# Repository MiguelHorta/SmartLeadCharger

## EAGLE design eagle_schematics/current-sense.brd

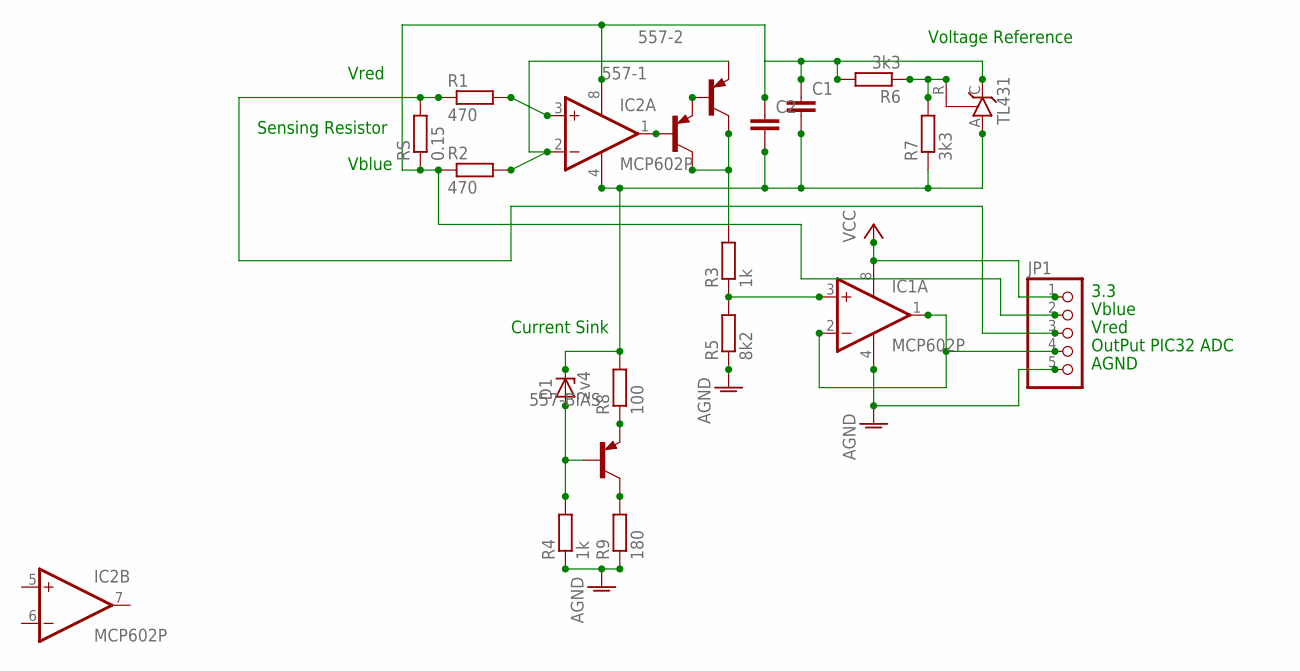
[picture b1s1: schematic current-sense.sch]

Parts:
557-1, 557-2, 557-BIAS: BC557A-PNP-TO92-EBC; TO92-EBC
C1, C2: C-EU075-032X103; C075-032X103
D1: 2v4; ZDIO-7.5
IC1, IC2: MCP602P; DIL08
JP1: PINHD-1X5; 1X05
R1, R2: 470; 0204/7
R3, R4: 1k; 0204/7
R5: 8k2; 0204/7
R6, R7: 3k3; 0204/7
R8: 100; 0204/7
R9: 180; 0204/7
RS: 0.15; VTA55
TL431: TL431CLP; TO92-CLP

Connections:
AGND: IC1.4 (V-), JP1.5, R5.1
unnamed: C1.2, C2.2, D1.C, IC2.4 (V-), R7.1, R8.2, TL431.A
unnamed: IC2.3 (+IN), R1.2
unnamed: 557-1.B, IC2.1 (OUT)
unnamed: 557-2.E, IC2.2 (-IN), R2.2
unnamed: 557-1.E, 557-2.B
unnamed: IC1.3 (+IN), R3.1, R5.2
unnamed: 557-1.C, 557-2.C, R3.2
unnamed: 557-BIAS.E, R8.1
unnamed: R6.1, R7.2, TL431.R
unnamed: 557-BIAS.C, R9.2
unnamed: 557-BIAS.B, D1.A, R4.2
unnamed: R4.1, R9.1
OUT: IC1.1 (OUT), IC1.2 (-IN), JP1.4
SN: C1.1, C2.1, IC2.8 (V+), JP1.2, R2.1, R6.2, RS.1, TL431.C
SP: JP1.3, R1.1, RS.2
VCC: IC1.8 (V+), JP1.1

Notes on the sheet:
3.3
AGND
OutPut PIC32 ADC
Vblue
Vred
Current Sink
Voltage Reference
Sensing Resistor

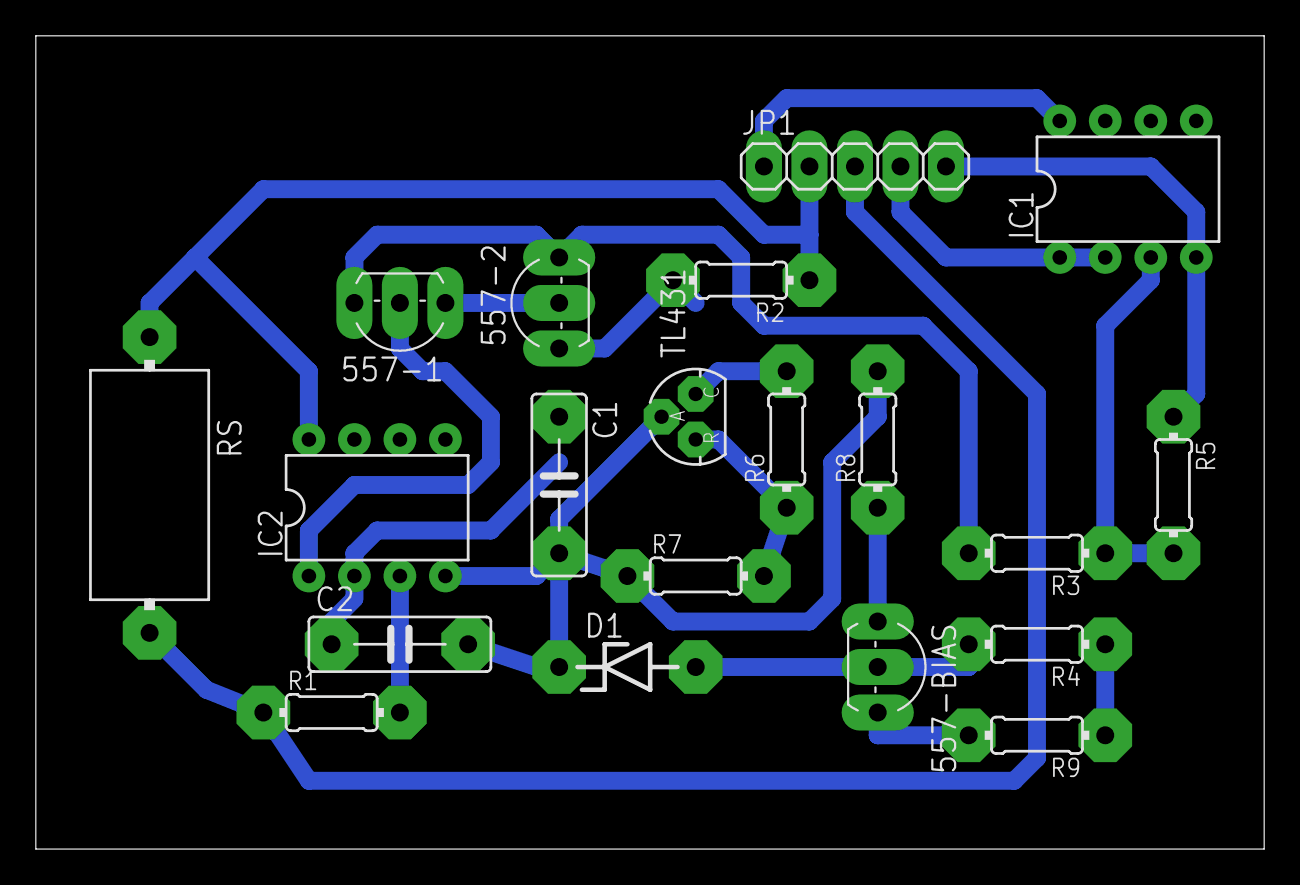
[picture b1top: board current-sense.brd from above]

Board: 2 copper layers, 68.6 x 45.4 mm, 20 parts (0 on the bottom side), 17 nets.

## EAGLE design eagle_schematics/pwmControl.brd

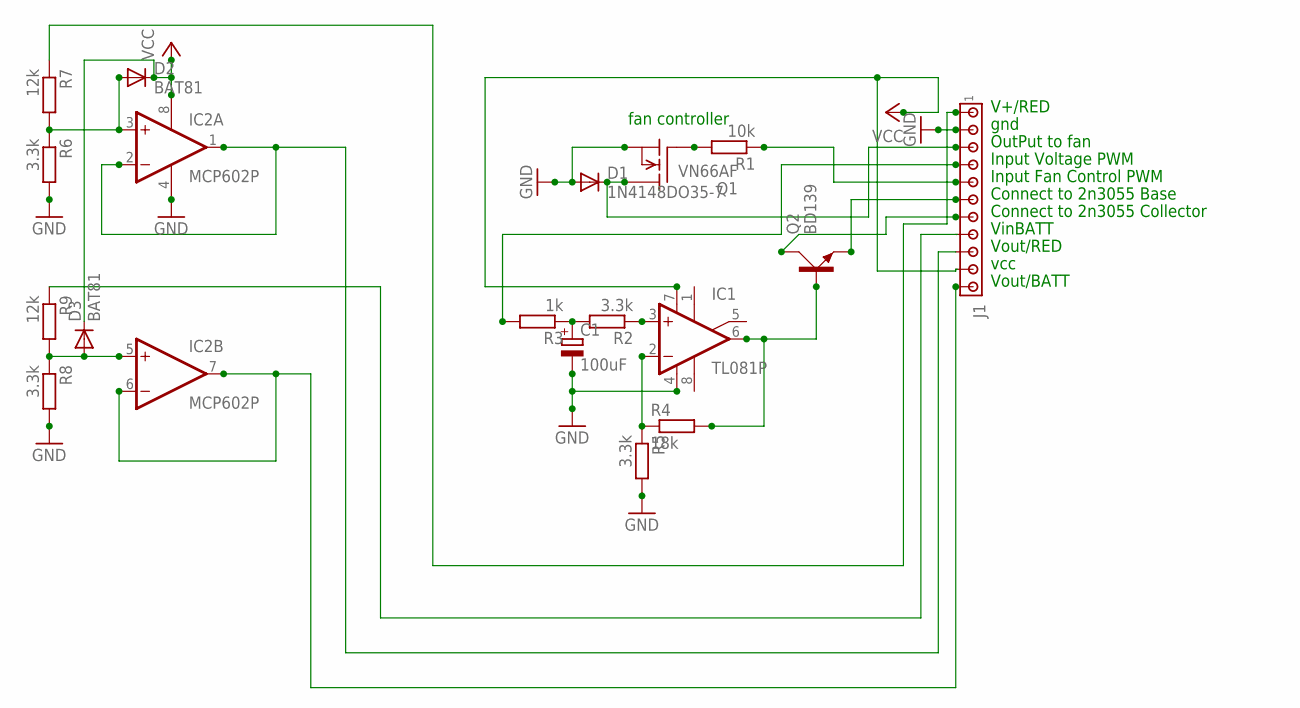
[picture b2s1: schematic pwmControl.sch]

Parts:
C1: 100uF; EB20D
D1: 1N4148DO35-7; DO35-7
D2, D3: BAT81; DO34-7
IC1: TL081P; DIL08
IC2: MCP602P; DIL08
J1: MTA11-156; 1X11MTA
Q1: VN66AF; TO202
Q2: BD139; TO126AV
R1: 10k; 0207/10
R2, R5, R6, R8: 3.3k; 0207/10
R3: 1k; 0207/10
R4: 18k; 0207/10
R7, R9: 12k; 0207/10

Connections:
2N3055BASE: J1.6, Q2.E
2N3055COL: J1.7, Q2.C
GND: C1.-, D1.A, IC1.4 (V-), IC2.4 (V-), J1.2, Q1.1 (S), R5.2, R6.2, R8.2
unnamed: Q1.2 (G), R1.2
unnamed: IC1.3 (+IN), R2.1
unnamed: C1.+, R2.2, R3.1
unnamed: IC1.2 (-IN), R4.1, R5.1
unnamed: IC1.6 (OUT), Q2.B, R4.2
unnamed: D2.A, IC2.3 (+IN), R6.1, R7.2
unnamed: D3.A, IC2.5 (+IN), R8.1, R9.2
OUTFAN: J1.5, R1.1
PWMFAN: D1.C, J1.3, Q1.3 (D)
PWMVOLTAGE: J1.4, R3.2
VCC: D2.C, D3.C, IC1.7 (V+), IC2.8 (V+), J1.10
VINBAT: J1.1, R7.1
VINRED: J1.8, R9.1
VOUTBATT: IC2.1 (OUT), IC2.2 (-IN), J1.9
VOUTRED: IC2.6 (-IN), IC2.7 (OUT), J1.11

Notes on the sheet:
fan controller
vcc
gnd
Input Fan Control PWM
OutPut to fan
Input Voltage PWM
Connect to 2n3055 Base
Connect to 2n3055 Collector
VinBATT
V+/RED
Vout/BATT
Vout/RED

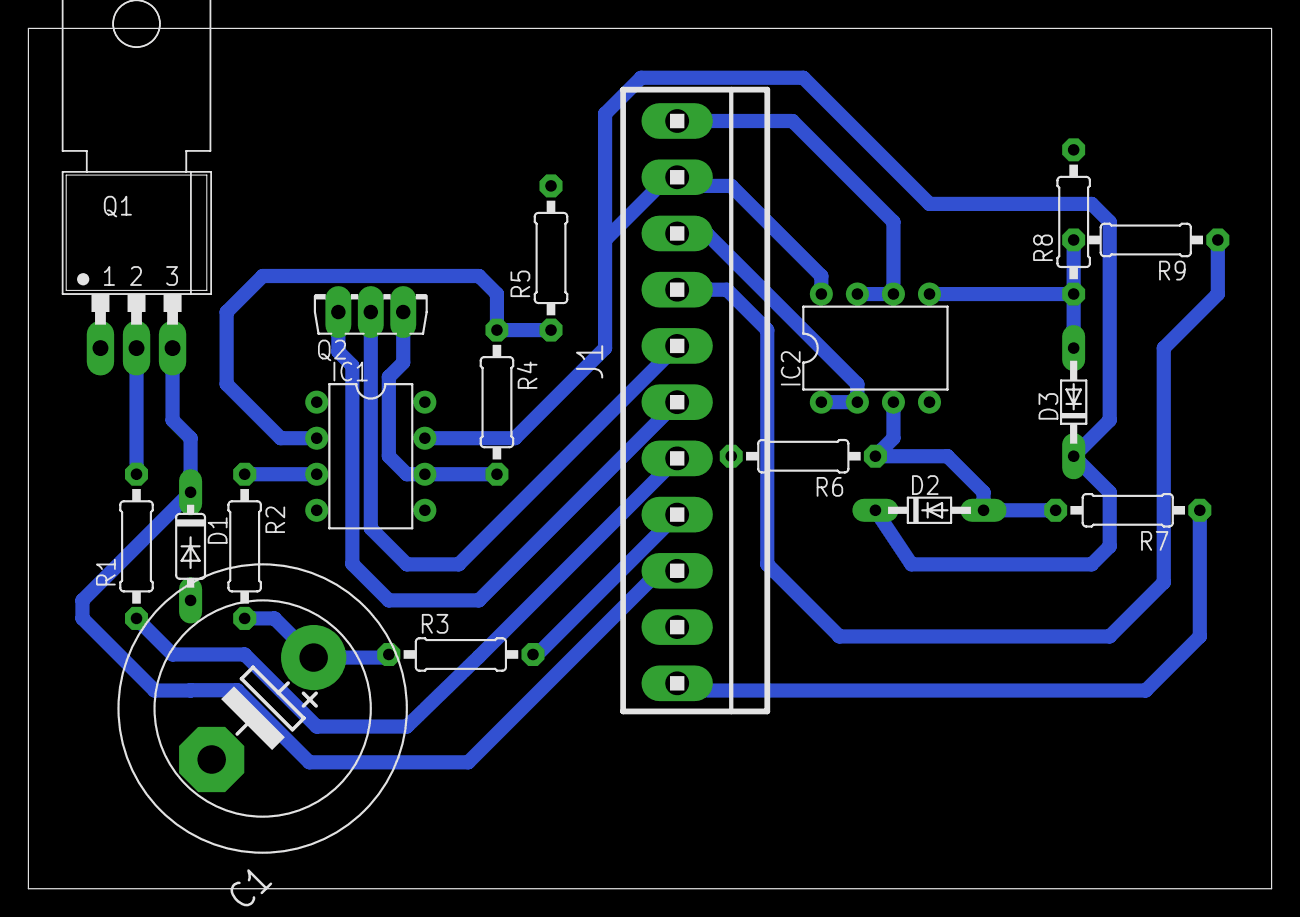
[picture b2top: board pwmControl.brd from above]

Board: 2 copper layers, 87.6 x 60.6 mm, 18 parts (0 on the bottom side), 18 nets.

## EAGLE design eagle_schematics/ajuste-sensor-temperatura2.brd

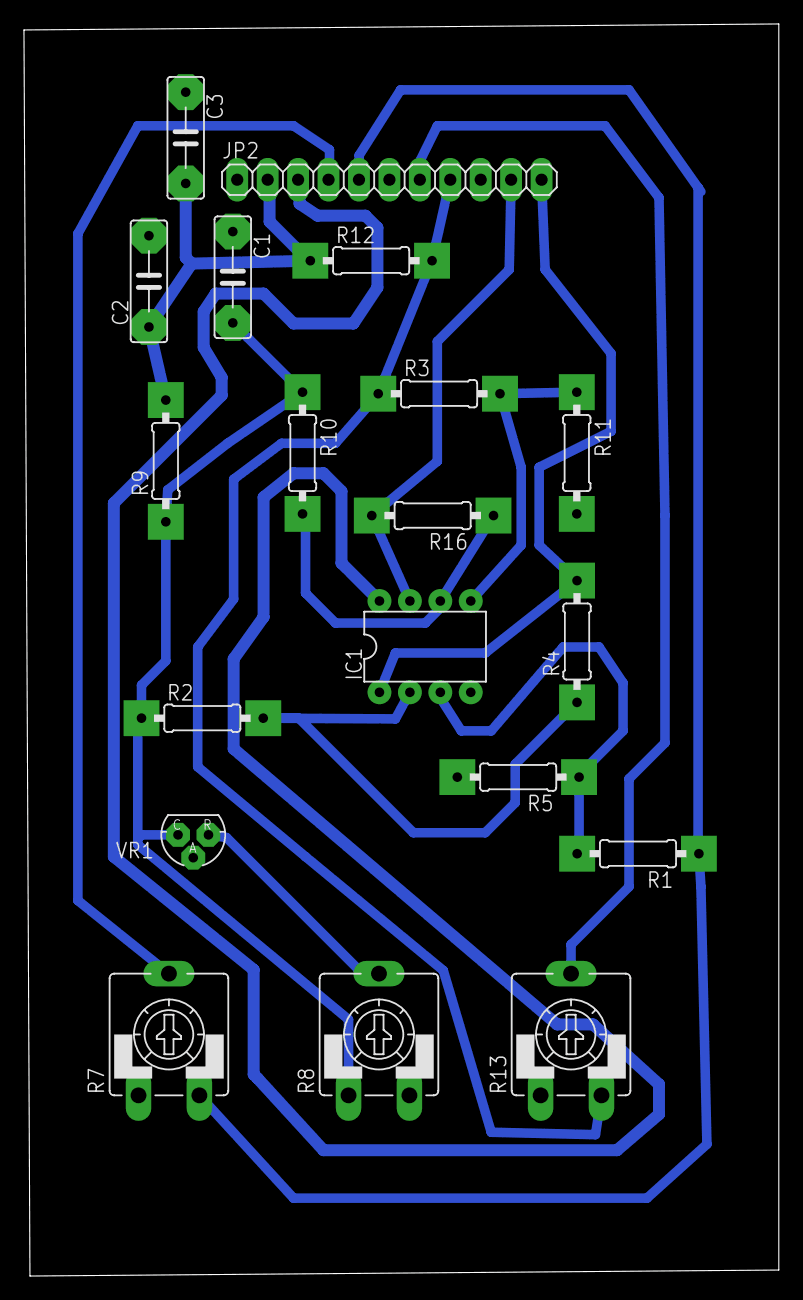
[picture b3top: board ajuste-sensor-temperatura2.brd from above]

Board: 2 copper layers, 63.0 x 104.5 mm, 19 parts (0 on the bottom side), 15 nets.

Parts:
C1, C2, C3: 0.01n; C7.5B3
IC1: MCP602P; DIL08
JP2: 1X11
R1, R2, R3, R10: 33k; 0207/10
R4, R5, R11, R16: 100k; 0207/10
R7, R13: 10k; CA9V
R8: 100; CA9V
R9: 120; 0207/10
R12: 330; 0207/10
VR1: 2.5V; TO92-CLP

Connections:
AGND: C1.1, C2.2, C3.1, IC1.4, JP2.1, JP2.6, JP2.9, R5.2, R7.A, R8.E, R11.2, R13.A, VR1.A
unnamed: IC1.3, R1.2, R5.1
unnamed: IC1.2, R2.2, R4.1
unnamed: JP2.5, R1.1, R7.E
unnamed: JP2.4, R7.S
unnamed: R8.S, VR1.R
unnamed: IC1.5, R3.2, R11.1
unnamed: IC1.6, R10.2, R16.1
unnamed: JP2.8, R3.1, R12.2, R13.E
unnamed: JP2.7, R13.S
unnamed: C1.2, R2.1, R8.A, R9.1, R10.1, VR1.C
OUT$1: IC1.1, JP2.11, R4.2
OUT$2: IC1.7, JP2.10, R16.2
S$1: C2.1, C3.2, JP2.2, R9.2, R12.1
VCC: IC1.8, JP2.3

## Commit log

2017-03-15 Commit de teste
2017-03-16 Finished ADC abstraction.
2017-03-16 Added printf functionality.
2017-03-16 Added PWM abstration.
2017-03-31 Test adc.
2017-04-06 Fix adc interruption routine.
2017-04-24 Fixed adc code. Implemented voltage regulator.
2017-04-25 Redo voltage regulator.
2017-04-25 Added bare bones for control loop.
2017-05-01 esquemático e placa em eagle dos sensores de temperatura
2017-05-01 esquematico e placa do medidor de corrente - Não está pronto a imprimir, tem que se alterar os MCP601X para op-amps que haja no armazem
2017-05-18 minor fixes
2017-05-22 Added display libs.
2017-05-23 Added some lcd entries.
2017-05-25 Lcd things
2017-05-25 Added charge panner.
2017-05-29 mais esquemáticos
2017-05-29 imagem com as DRC
2017-06-01 Cantos 3D Model
2017-06-01 gcode 3D model
2017-06-05 Debug related additions.
2017-06-05 algoritmo de controlo introduzido
2017-06-07 Loop control improvment.
2017-06-08 Sprint.
2017-06-08 Sprint..
2017-06-21 Bump
2017-06-22 User manual progress.
2017-06-22 Finished User guide.
2017-06-22 Added deliverables structure.
2017-06-23 Fixed typos.
2017-06-23 RelatorioFinal
2017-06-23 atualizacao de modelos 3D e esquematicos
2017-06-23 Apresentacao
